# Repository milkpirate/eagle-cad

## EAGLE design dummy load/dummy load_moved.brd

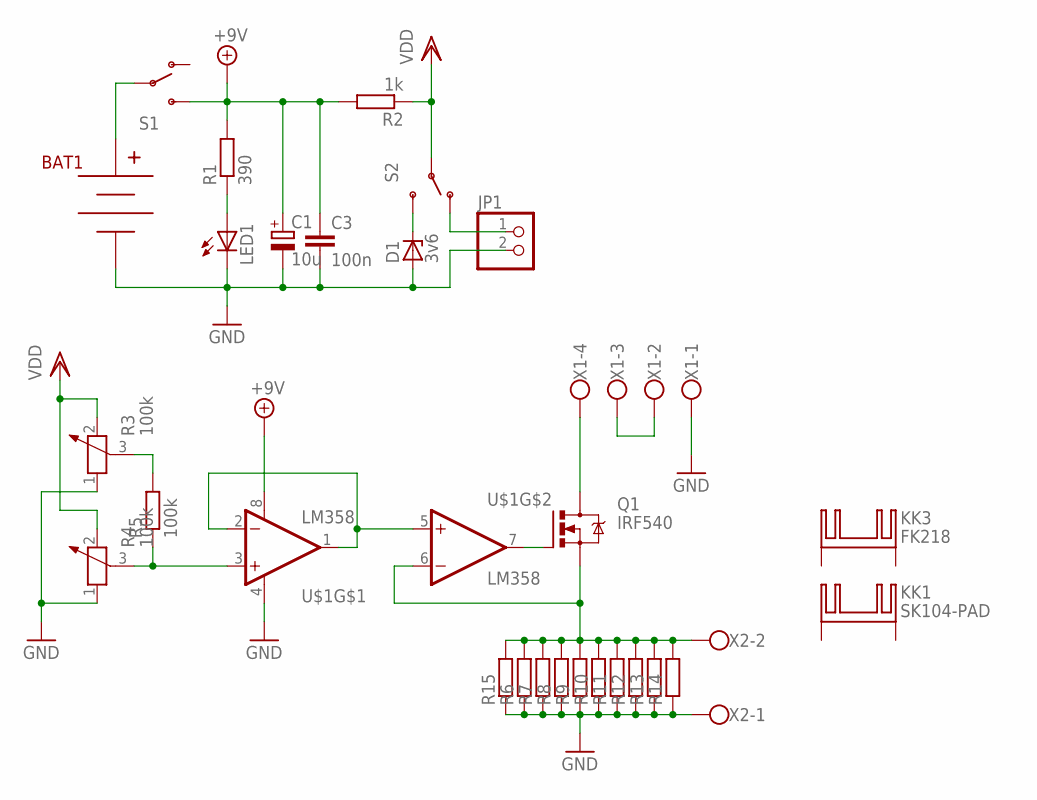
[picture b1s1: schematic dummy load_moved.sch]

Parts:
BAT1: BC9VPC
C1: 10u; TT2D5L
C3: 100n; C025-025X050
D1: 3v6; ZDIO-5
JP1: PINHD-1X2; 1X02
KK1: SK104-PAD
KK3: FK218
LED1: LED5MM
Q1: IRF540; TO220BV
R1: 390; 0204/7
R2: 1k; 0204/7
R3, R4: 100k; PT-10
R5: 100k; 0204/7
R6, R7, R8, R9, R10, R11, R12, R13, R14, R15: R-EU_0207/7; 0207/7
S1, S2: SWITCH-SPSTPTH; SWITCH-SPDT
U$1: LM358; DIP08
X1: W237-4
X2: W237-102

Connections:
+9V: C1.+, C3.1, R1.2, R2.2, S1.3 (S), U$1.8 (V+)
GND: BAT1.V-, C1.-, C3.2, D1.A, JP1.2, LED1.K (C), R3.1, R4.1, R6.1, R7.1, R8.1, R9.1, R10.1, R11.1, R12.1, R13.1, R14.1, R15.1, U$1.4 (V-), X1.1, X2.1
unnamed: U$1.1 (OUT), U$1.2 (-IN), U$1.5 (+IN)
unnamed: R4.3, R5.1, U$1.3 (+IN)
unnamed: LED1.A, R1.1
unnamed: R3.3, R5.2
unnamed: BAT1.V+, S1.2
unnamed: Q1.D, X1.4
unnamed: X1.2, X1.3
unnamed: Q1.G, U$1.7 (OUT)
unnamed: D1.C, S2.3 (S)
unnamed: JP1.1, S2.1 (O)
unnamed: Q1.S, R6.2, R7.2, R8.2, R9.2, R10.2, R11.2, R12.2, R13.2, R14.2, R15.2, U$1.6 (-IN), X2.2
VDD: R2.1, R3.2, R4.2, S2.2

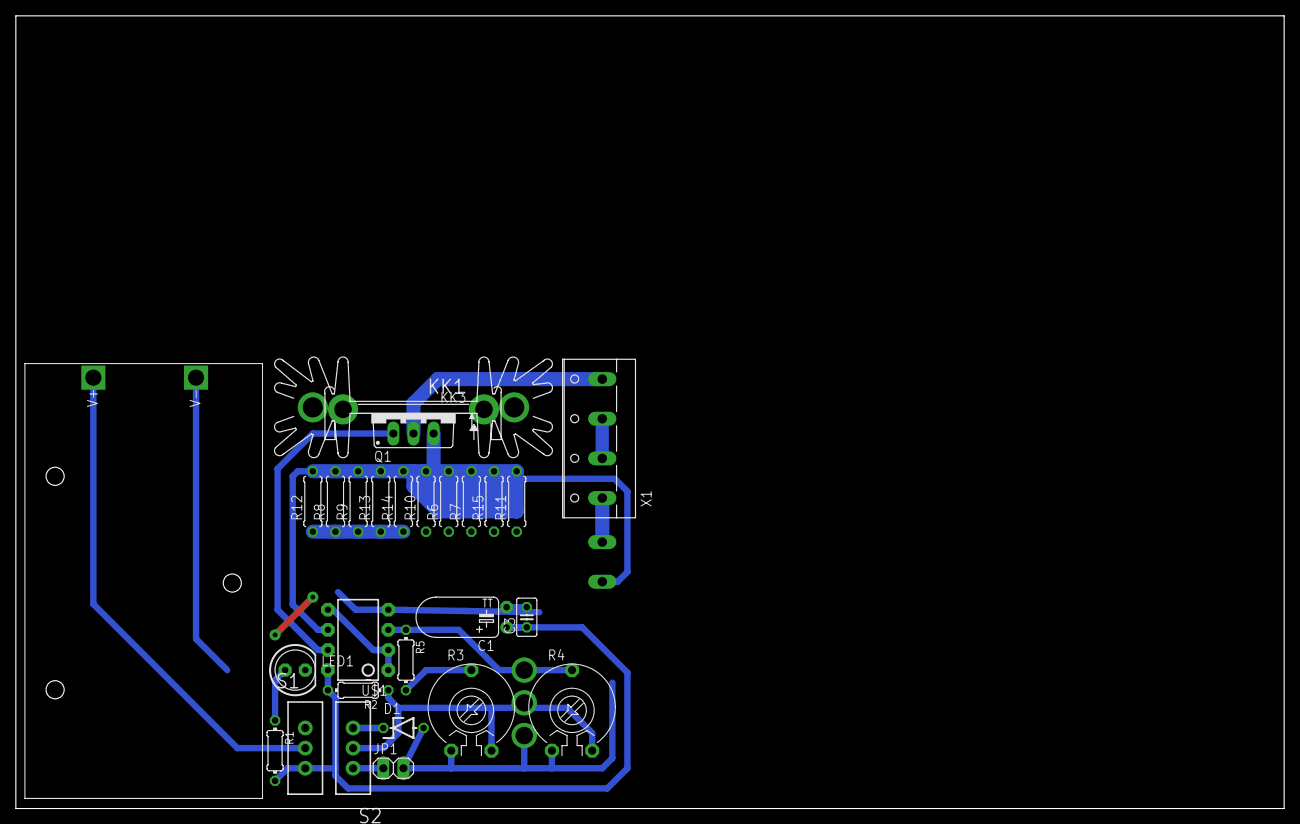
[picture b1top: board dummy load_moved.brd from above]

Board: 2 copper layers, 160.0 x 100.0 mm, 29 parts (1 on the bottom side), 14 nets.

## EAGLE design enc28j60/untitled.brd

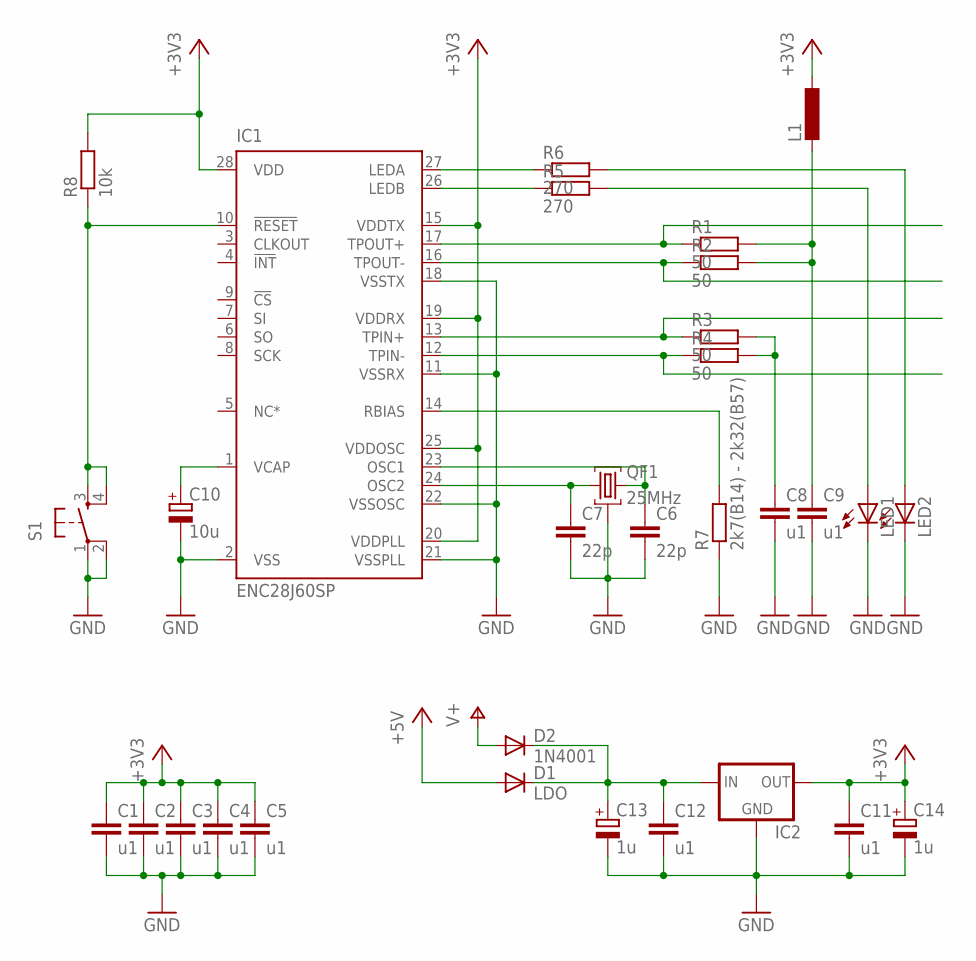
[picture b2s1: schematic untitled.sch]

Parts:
C1, C2, C3, C4, C5, C8, C9, C11, C12: u1; C025-025X050
C6, C7: 22p; C025-025X050
C10: 10u; E2,5-6
C13, C14: 1u; E2,5-6
D1: LDO; D-2.5
D2: 1N4001; D-2.5
IC1: ENC28J60SP; DIL28-3
IC2: MCP1700_TO92-INLINE; TO92-
L1: L-EU0204/5; 0204/5
LED1, LED2: LED5MM
QF1: 25MHz; HC49U
R1, R2, R3, R4: 50; 0204/7
R5, R6: 270; 0204/7
R7: 2k7(B14) - 2k32(B57); 0204/7
R8: 10k; 0204V
S1: TAC_SWITCHPTH; TACTILE-PTH

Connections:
+3V3: C1.1, C2.1, C3.1, C4.1, C5.1, C11.1, C14.+, IC1.15 (VDDTX), IC1.19 (VDDRX), IC1.20 (VDDPLL), IC1.25 (VDDOSC), IC1.28 (VDD), IC2.3 (OUT), L1.1, R8.2
+5V: D1.A
GND: C1.2, C2.2, C3.2, C4.2, C5.2, C6.2, C7.2, C8.2, C9.2, C10.-, C11.2, C12.2, C13.-, C14.-, IC1.2 (VSS), IC1.11 (VSSRX), IC1.18 (VSSTX), IC1.21 (VSSPLL), IC1.22 (VSSOSC), IC2.1 (GND), LED1.K (C), LED2.K (C), QF1.2, R7.1, S1.1, S1.2
unnamed: C10.+, IC1.1 (VCAP)
unnamed: C8.1, R3.2, R4.2
unnamed: IC1.27 (LEDA), R6.1
unnamed: IC1.26 (LEDB), R5.1
unnamed: IC1.17 (TPOUT+), R1.1
unnamed: C7.1, IC1.24 (OSC2), QF1.1
unnamed: C6.1, IC1.23 (OSC1), QF1.3
unnamed: IC1.16 (TPOUT-), R2.1
unnamed: IC1.14 (RBIAS), R7.2
unnamed: IC1.13 (TPIN+), R3.1
unnamed: IC1.12 (TPIN-), R4.1
unnamed: LED1.A, R5.2
unnamed: C9.1, L1.2, R1.2, R2.2
unnamed: LED2.A, R6.2
unnamed: C12.1, C13.+, D1.C, D2.C, IC2.2 (IN)
unnamed: IC1.10 (!RESET), R8.1, S1.3, S1.4
V+: D2.A

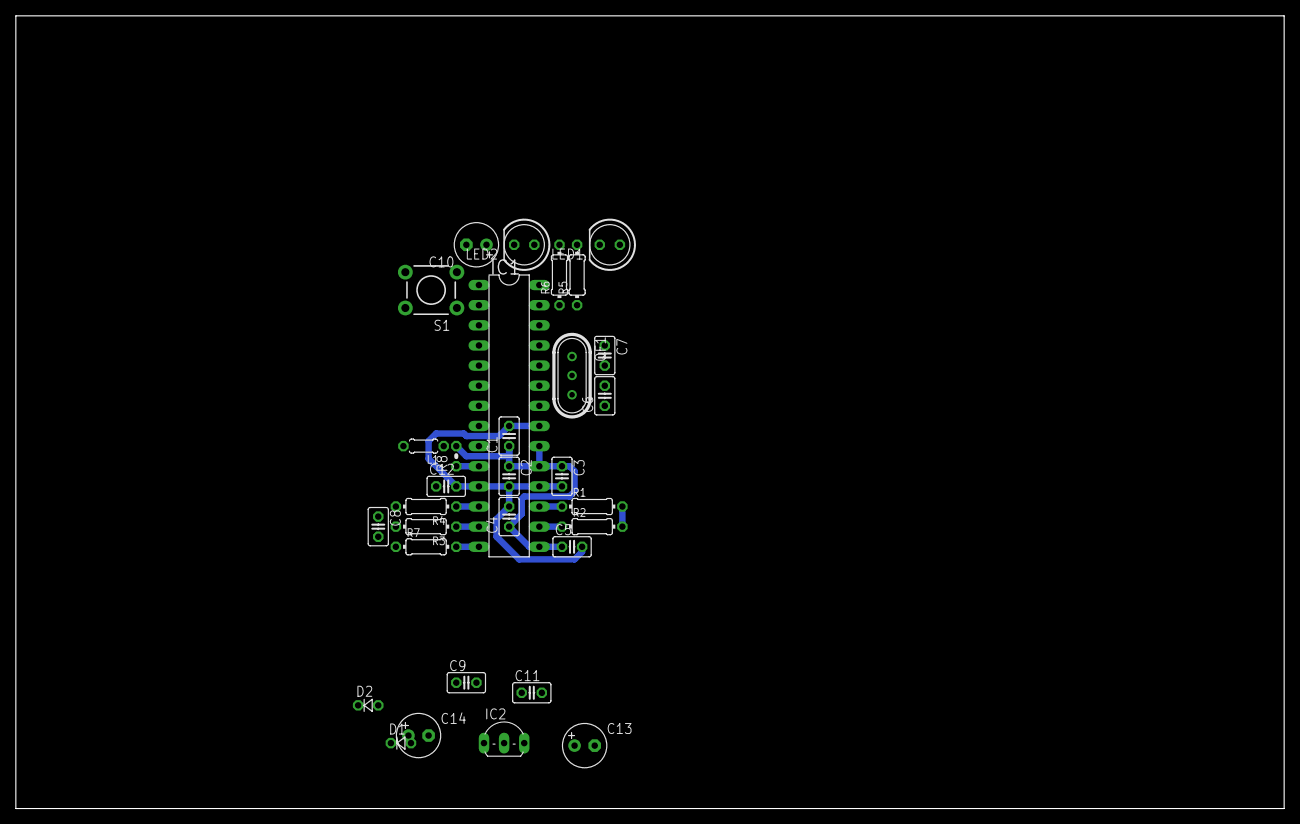
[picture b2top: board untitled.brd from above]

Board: 2 copper layers, 160.0 x 100.0 mm, 31 parts (0 on the bottom side), 18 nets.

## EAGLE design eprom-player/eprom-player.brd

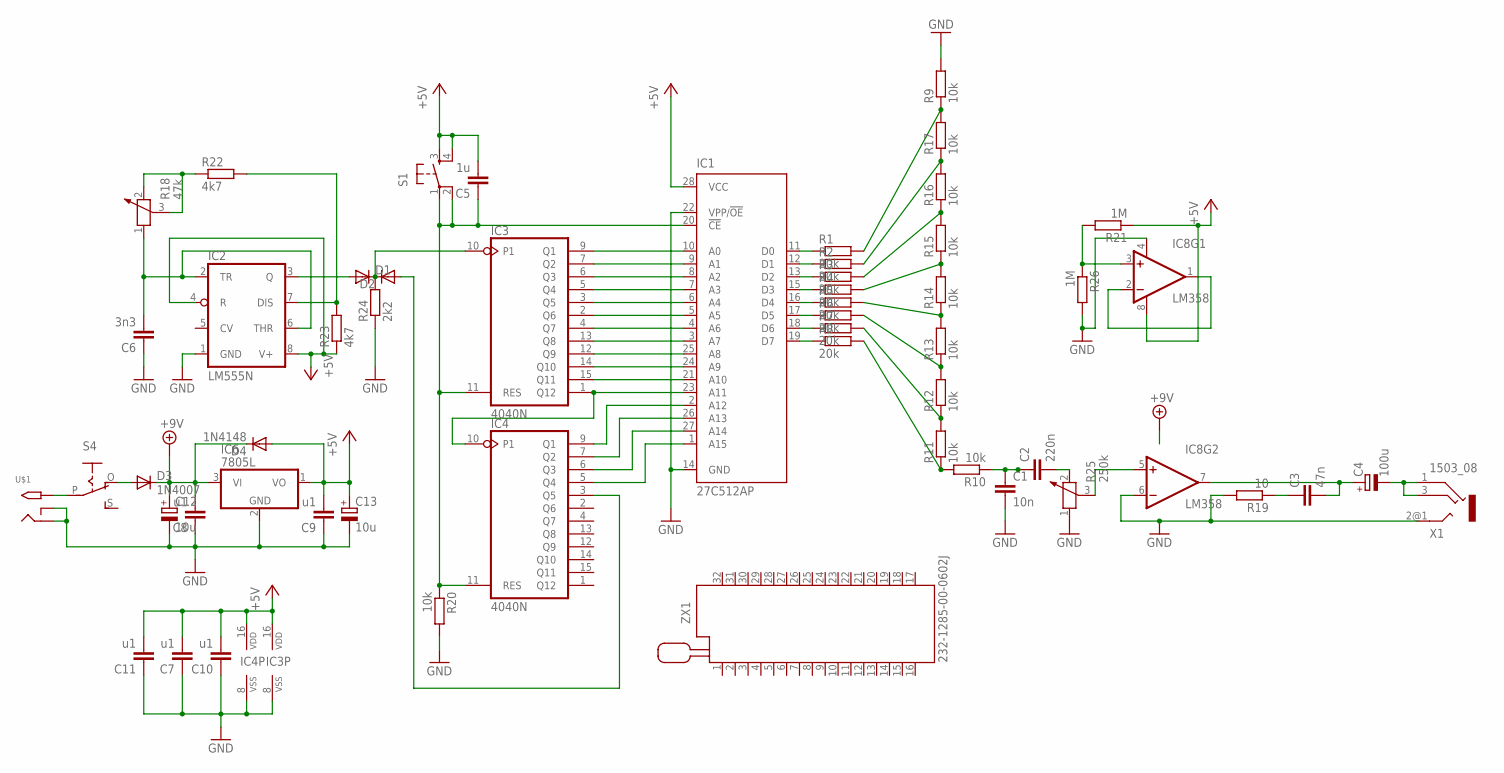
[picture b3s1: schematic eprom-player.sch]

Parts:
C1: 10n; C025-025X050
C2: 220n; C025-025X050
C3: 47n; C025-025X050
C4: 100u; E2,5-5
C5: 1u; C025-025X050
C6: 3n3; C025-025X050
C7, C8, C9, C10, C11: u1; C025-025X050
C12, C13: 10u; E2,5-6
D1, D2: DIODE-D-7.5; D-7.5
D3: 1N4007; D-2.5
D4: 1N4148; D-2.5
IC1: 27C512AP; DIL28-6
IC2: LM555N; DIL08-ROUND
IC3, IC4: 4040N; DIL16
IC6: 7805L; TO92
IC8: LM358; DIP08
R1, R2, R3: 20k; 0204/7
R4, R5, R6, R7, R8: 20k; 0204V
R9, R10, R11, R12, R13, R14, R15, R16, R17, R20: 10k; 0204V
R18: 47k; PT-10
R19: 10; 0204/5
R21, R26: 1M; 0204V
R22, R23: 4k7; 0204V
R24: 2k2; 0204V
R25: 250k; PT-10
S1: TAC_SWITCHPTH; TACTILE-PTH
S4: EG1218S; EG1218
U$1: 2.1MMJACKTHM; PJ-102A
X1: 1503_08
ZX1: 232-1285-00-0602J

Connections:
+5V: C5.2, C7.2, C9.2, C10.2, C11.2, C13.+, D4.A, IC1.28 (VCC), IC2.4 (R), IC2.8 (V+), IC3.16 (VDD), IC4.16 (VDD), IC6.1 (VO), IC8.8 (V+), R21.1, R23.1, S1.3, S1.4
+9V: C8.2, C12.+, D3.C, D4.C, IC6.3 (VI)
GND: C1.2, C6.1, C7.1, C8.1, C9.1, C10.1, C11.1, C12.-, C13.-, IC1.14 (GND), IC1.22 (VPP/!OE), IC2.1 (GND), IC3.8 (VSS), IC4.8 (VSS), IC6.2 (GND), IC8.4 (V-), IC8.6 (-IN), R9.2, R19.2, R20.2, R24.1, R25.1, R26.2, U$1.RING, U$1.RING_SW, X1.2@1 (2)
unnamed: IC1.11 (D0), R1.1
unnamed: IC1.12 (D1), R2.1
unnamed: IC1.13 (D2), R3.1
unnamed: IC1.15 (D3), R4.1
unnamed: IC1.16 (D4), R5.1
unnamed: IC1.17 (D5), R6.1
unnamed: IC1.18 (D6), R7.1
unnamed: IC1.19 (D7), R8.1
unnamed: IC1.23 (A11), IC3.1 (Q12), IC4.10 (P1)
unnamed: IC1.5 (A5), IC3.2 (Q6)
unnamed: IC1.6 (A4), IC3.3 (Q5)
unnamed: IC1.4 (A6), IC3.4 (Q7)
unnamed: IC1.7 (A3), IC3.5 (Q4)
unnamed: IC1.8 (A2), IC3.6 (Q3)
unnamed: IC1.9 (A1), IC3.7 (Q2)
unnamed: IC1.10 (A0), IC3.9 (Q1)
unnamed: IC1.25 (A8), IC3.12 (Q9)
unnamed: IC1.3 (A7), IC3.13 (Q8)
unnamed: IC1.24 (A9), IC3.14 (Q10)
unnamed: IC1.21 (A10), IC3.15 (Q11)
unnamed: IC1.2 (A12), IC4.9 (Q1)
unnamed: IC1.26 (A13), IC4.7 (Q2)
unnamed: IC1.27 (A14), IC4.6 (Q3)
unnamed: IC1.1 (A15), IC4.5 (Q4)
unnamed: R8.2, R10.2, R11.1
unnamed: R7.2, R11.2, R12.1
unnamed: R5.2, R13.2, R14.1
unnamed: R4.2, R14.2, R15.1
unnamed: R2.2, R16.2, R17.1
unnamed: R6.2, R12.2, R13.1
unnamed: R3.2, R15.2, R16.1
unnamed: R1.2, R9.1, R17.2
unnamed: C1.1, C2.1, R10.1
unnamed: C2.2, R25.2
unnamed: C4.-, X1.1, X1.3
unnamed: IC8.5 (+IN), R25.3
unnamed: C3.1, R19.1
unnamed: C3.2, C4.+, IC8.7 (OUT)
unnamed: C5.1, IC1.20 (!CE), IC3.11 (RES), IC4.11 (RES), R20.1, S1.1, S1.2
unnamed: D1.C, D2.C, IC3.10 (P1), R24.2
unnamed: D1.A, IC2.3 (Q)
unnamed: C6.2, IC2.2 (TR), IC2.6 (THR), R18.1
unnamed: S4.P, U$1.TIP
unnamed: R18.2, R18.3, R22.1
unnamed: IC2.7 (DIS), R22.2, R23.2
unnamed: D2.A, IC4.3 (Q5)
unnamed: D3.A, S4.O
unnamed: IC8.1 (OUT), IC8.2 (-IN)
unnamed: IC8.3 (+IN), R21.2, R26.1

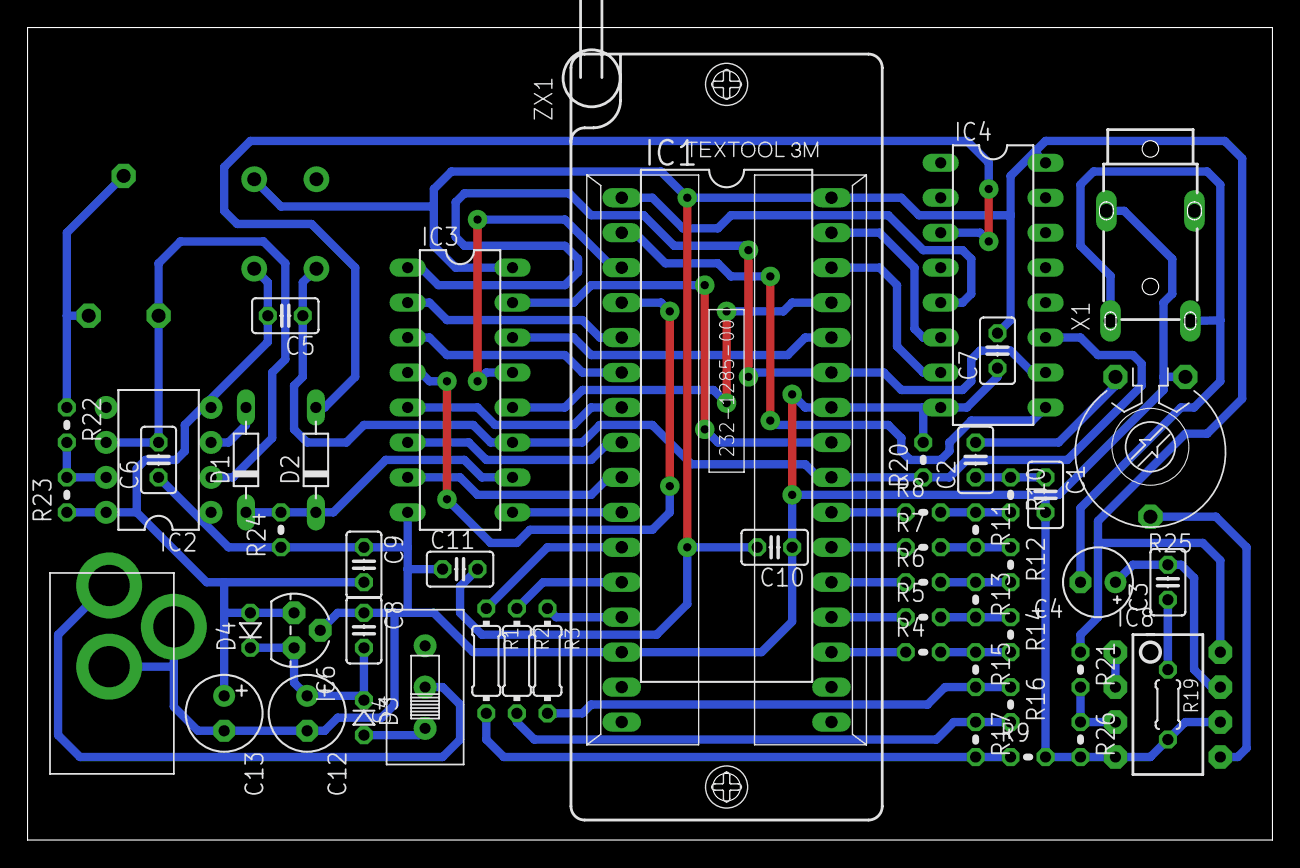
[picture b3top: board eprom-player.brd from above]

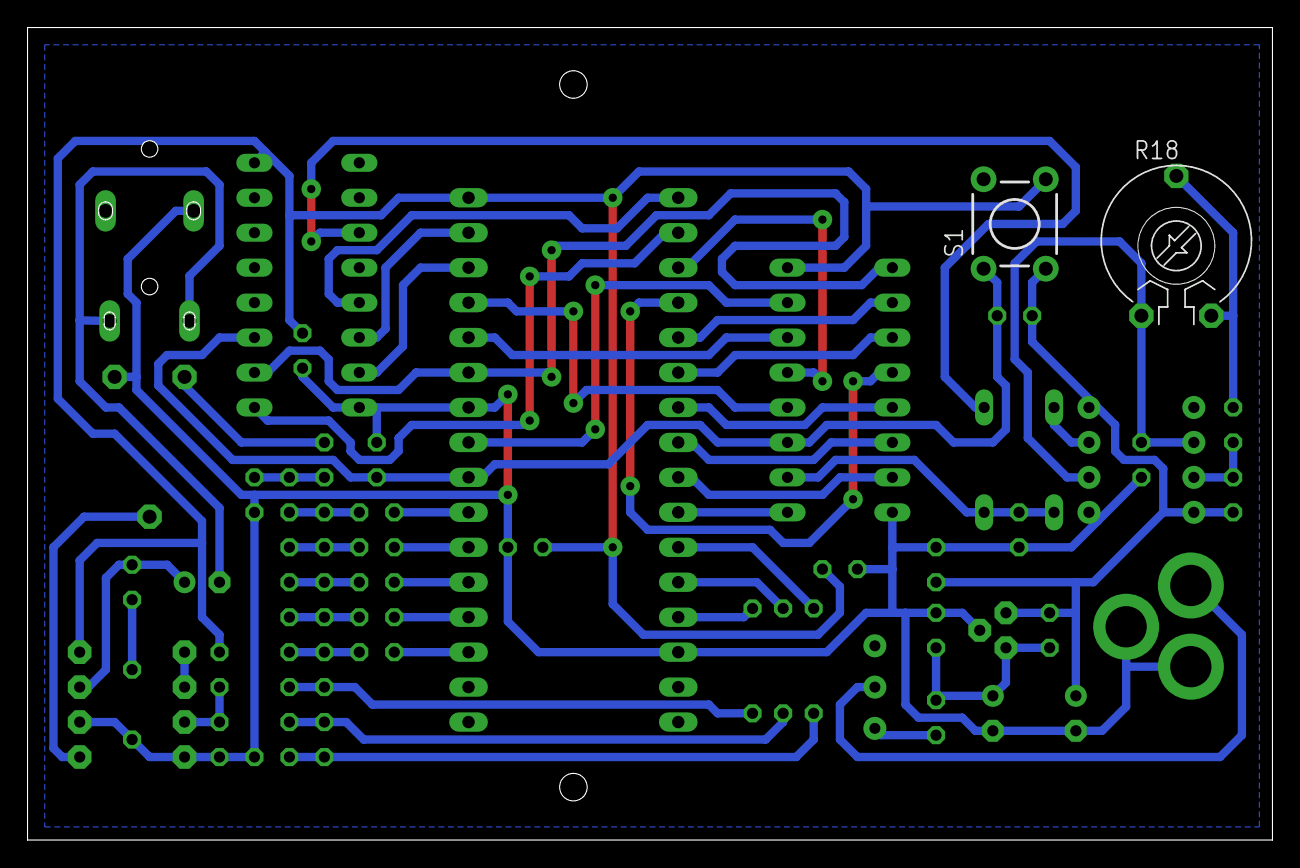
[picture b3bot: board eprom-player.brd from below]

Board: 2 copper layers, 90.5 x 59.0 mm, 54 parts (2 on the bottom side), 52 nets.

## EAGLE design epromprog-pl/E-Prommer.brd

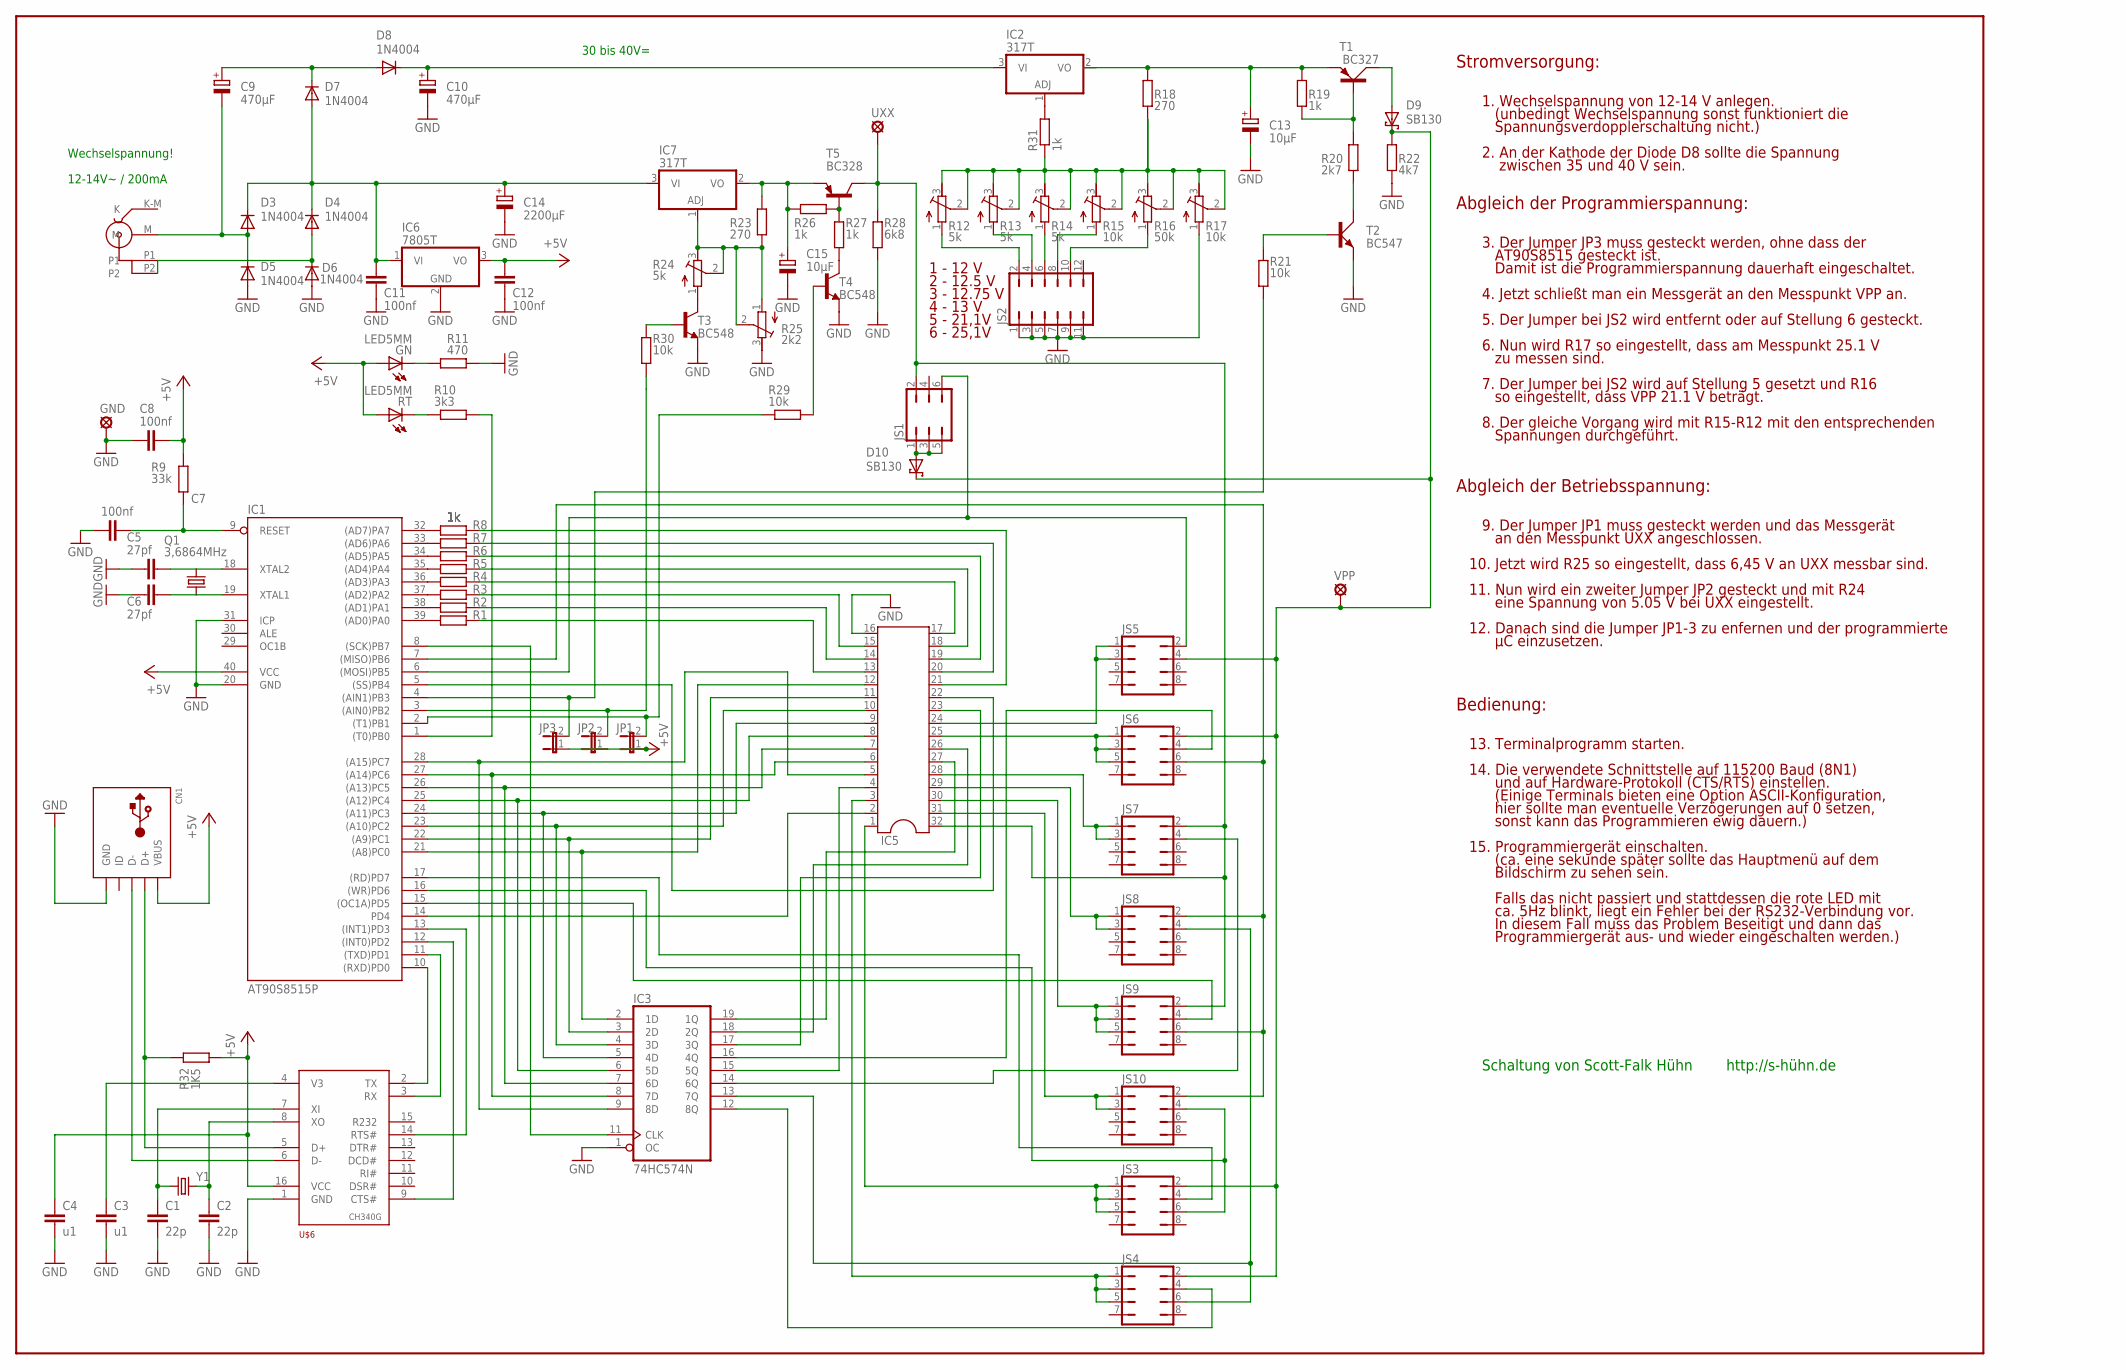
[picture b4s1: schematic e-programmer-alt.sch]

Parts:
BU1: KLIN_BU
C1, C2: 22p; C025-025X050
C3, C4: u1; C025-025X050
C5, C6: 27pf; C025-024X044
C7, C8, C11, C12: 100nf; C025-024X044
C9: 470µF; E3,5-10
C10: 470µF; E5-13
C13: 10µF; E2,5-5
C14: 2200µF; E7,5-16
C15: 10µF; E5-5
CN1: USBTHM; USB-MINIB-THM
D3, D4, D5, D6, D7, D8: 1N4004; DO41-10
D9, D10: SB130; DO35-7
GN: LED5MM
GND: LSP10
IC1: AT90S8515P; DIL40
IC2, IC7: 317T; TO220H
IC3: 74HC574N; DIL20
IC5: DIL32
IC6: 7805T; TO220H
JP1, JP2, JP3: JP1E; JP1
JS1: JP3Q
JS2: JP6Q
JS3, JS4, JS5, JS6, JS7, JS8, JS9, JS10: JP4Q
Q1: 3,6864MHz; HC49U-V
R1, R2, R3, R4, R5, R6, R7, R8, R19, R26, R27, R31: 1k; 0207/7
R9: 33k; 0204/7
R10: 3k3; 0204/7
R11: 470; 0204/7
R12, R13, R14, R24: 5k; RTRIM3296Y
R15, R17: 10k; RTRIM3296Y
R16: 50k; RTRIM3296Y
R18, R23: 270; 0207/7
R20: 2k7; 0207/7
R21, R29, R30: 10k; 0207/7
R22: 4k7; 0207/7
R25: 2k2; RTRIM3296Y
R28: 6k8; 0207/7
R32: 1K5; 0204/7
RT: LED5MM
T1: BC327; SOT54A
T2: BC547; SOT54A
T3, T4: BC548; TO92
T5: BC328; TO92
U$6: CH340G; SO16
UXX: LSP10
VPP: LSP10
Y1: CRYSTALHC49US; HC49US

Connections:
!CE: IC1.5 ((SS)PB4), IC5.22
!OE: IC1.6 ((MOSI)PB5), JS1.6, JS5.2
!PR: IC1.7 ((MISO)PB6), JS6.6, JS8.2, JS9.6, JS10.2
+5V: C4.1, C8.2, C12.1, CN1.VBUS, GN.A, IC1.40 (VCC), IC6.3 (VO), JP1.1, JP2.1, JP3.1, R9.2, R32.1, RT.A, U$6.16 (VCC); also elsewhere on the board
A0: IC1.21 ((A8)PC0), IC3.2 (1D), IC5.12
A1: IC1.22 ((A9)PC1), IC3.3 (2D), IC5.11
A2: IC1.23 ((A10)PC2), IC3.4 (3D), IC5.10
A3: IC1.24 ((A11)PC3), IC3.5 (4D), IC5.9
A4: IC1.25 ((A12)PC4), IC3.6 (5D), IC5.8
A5: IC1.26 ((A13)PC5), IC3.7 (6D), IC5.7
A6: IC1.27 ((A14)PC6), IC3.8 (7D), IC5.6
A7: IC1.28 ((A15)PC7), IC3.9 (8D), IC5.5
A8: IC3.19 (1Q), IC5.27
A9: IC3.18 (2Q), IC5.26
A10: IC3.17 (3Q), IC5.23
A11: IC3.16 (4Q), JS6.4
A12: IC3.15 (5Q), IC5.4
A13: IC3.14 (6Q), JS7.4
A14: IC3.13 (7Q), JS4.6, JS8.4
A15: IC3.12 (8Q), JS4.4
A16: IC1.14 (PD4), IC5.2
A17: IC1.15 ((OC1A)PD5), JS9.4
A18: IC1.16 ((WR)PD6), JS3.6, JS10.4
A19: IC1.17 ((RD)PD7), JS3.4
CTS: IC1.12 ((INT0)PD2), U$6.9 (CTS#); also elsewhere on the board
D0: IC5.13, R1.2
D1: IC5.14, R2.2
D2: IC5.15, R3.2
D3: IC5.17, R4.2
D4: IC5.18, R5.2
D5: IC5.19, R6.2
D6: IC5.20, R7.2
D7: IC5.21, R8.2
GND: C1.2, C2.2, C3.2, C4.2, C5.1, C6.1, C7.1, C8.1, C10.-, C11.2, C12.2, C13.-, C14.-, C15.-, CN1.GND, D5.A, D6.A, GND.MP, IC1.20 (GND), IC1.31 (ICP), IC3.1 (OC), IC5.16, IC6.2 (GND), JS2.1, JS2.3, JS2.5, JS2.7, JS2.9, JS2.11, R11.2, R17.1 (E), R22.1, R25.3 (A), R28.1, T2.E, T3.1 (E), T4.1 (E), U$6.1 (GND); also elsewhere on the board
unnamed: IC1.32 ((AD7)PA7), R8.1
unnamed: IC1.33 ((AD6)PA6), R7.1
unnamed: IC1.34 ((AD5)PA5), R6.1
unnamed: IC1.35 ((AD4)PA4), R5.1
unnamed: IC1.36 ((AD3)PA3), R4.1
unnamed: IC1.37 ((AD2)PA2), R3.1
unnamed: IC1.38 ((AD1)PA1), R2.1
unnamed: IC1.39 ((AD0)PA0), R1.1
unnamed: IC1.8 ((SCK)PB7), IC3.11 (CLK)
unnamed 43: IC1.10 ((RXD)PD0), U$6.2 (TX); also elsewhere on the board
unnamed 44: IC1.11 ((TXD)PD1), U$6.3 (RX); also elsewhere on the board
unnamed: CN1.D+, R32.2, U$6.5 (D+)
unnamed: CN1.D-, U$6.6 (D-)
unnamed: C2.1, U$6.8 (XO), Y1.2
unnamed: C1.1, U$6.7 (XI), Y1.1
unnamed: C3.1, U$6.4 (V3)
unnamed: R10.1, RT.K (C)
unnamed: GN.K (C), R11.1
unnamed: IC5.3, JS4.1, JS4.3, JS4.5
unnamed: IC5.1, JS3.1, JS3.3, JS3.5
unnamed: IC5.24, JS5.1, JS5.3
unnamed: C7.2, IC1.9 (RESET), R9.1
unnamed: IC5.25, JS6.1, JS6.3, JS6.5
unnamed: JS2.2, R12.1 (E)
unnamed: JS2.4, R13.1 (E)
unnamed: IC5.28, JS7.1, JS7.3
unnamed: IC5.29, JS8.1, JS8.3
unnamed: IC1.1 ((T0)PB0), R10.2
unnamed: IC5.30, JS9.1, JS9.3, JS9.5
unnamed: JS2.6, R14.1 (E)
unnamed: IC5.31, JS10.1, JS10.3
unnamed: JS2.8, R15.1 (E)
unnamed: JS2.10, R16.1 (E)
unnamed 71: R12.2 (S), R12.3 (A), R13.2 (S), R13.3 (A), R14.2 (S), R14.3 (A), R15.2 (S), R15.3 (A), R16.2 (S), R16.3 (A), R17.2 (S), R17.3 (A), R18.1, R31.1; also elsewhere on the board
unnamed: D10.A, JS1.1, JS1.3, JS1.5
unnamed: D9.A, T1.C
unnamed: R26.1, R27.2, T5.2 (B)
unnamed: R27.1, T4.3 (C)
unnamed: IC7.1 (ADJ), R23.1, R24.2 (S), R24.3 (A), R25.1 (E), R25.2 (S)
unnamed: R24.1 (E), T3.3 (C)
unnamed: C15.+, IC7.2 (VO), R23.2, R26.2, T5.1 (E)
unnamed: R29.2, T4.2 (B)
unnamed: C13.+, IC2.2 (VO), R18.2, R19.2, T1.E
unnamed: R30.2, T3.2 (B)
unnamed: R19.1, R20.2, T1.B
unnamed: R20.1, T2.C
unnamed: R21.2, T2.B
unnamed: IC2.1 (ADJ), R31.2
RTS: IC1.13 ((INT1)PD3), U$6.14 (RTS#); also elsewhere on the board
UXX: IC5.32, JS1.2, JS7.2, JS9.2, R28.2, T5.3 (C), UXX.MP
VCC_5/6: IC1.3 ((AIN0)PB2), JP2.2, R30.1
VCC_EIN: IC1.2 ((T1)PB1), JP1.2, R29.1
VPP: D9.C, D10.C, JS3.2, JS4.2, JS5.4, JS6.2, R22.2, VPP.MP
VPP_EIN: IC1.4 ((AIN1)PB3), JP3.2, R21.1

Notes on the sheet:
12-14V~ / 200mA
Wechselspannung!
30 bis 40V=
Schaltung von Scott-Falk Hühn
http://s-hühn.de
1. Wechselspannung von 12-14 V anlegen.
(unbedingt Wechselspannung sonst funktioniert die
Spannungsverdopplerschaltung nicht.)
2. An der Kathode der Diode D8 sollte die Spannung
zwischen 35 und 40 V sein.
3. Der Jumper JP3 muss gesteckt werden, ohne dass der
4. Jetzt schließt man ein Messgerät an den Messpunkt VPP an.
5. Der Jumper bei JS2 wird entfernt oder auf Stellung 6 gesteckt.
6. Nun wird R17 so eingestellt, dass am Messpunkt 25.1 V
zu messen sind.
7. Der Jumper bei JS2 wird auf Stellung 5 gesetzt und R16
so eingestellt, dass VPP 21.1 V beträgt.
8. Der gleiche Vorgang wird mit R15-R12 mit den entsprechenden
Spannungen durchgeführt.
9. Der Jumper JP1 muss gesteckt werden und das Messgerät
an den Messpunkt UXX angeschlossen.
10. Jetzt wird R25 so eingestellt, dass 6,45 V an UXX messbar sind.
11. Nun wird ein zweiter Jumper JP2 gesteckt und mit R24
eine Spannung von 5.05 V bei UXX eingestellt.
Abgleich der Programmierspannung:
Abgleich der Betriebsspannung:
Bedienung:
13. Terminalprogramm starten.
14. Die verwendete Schnittstelle auf 115200 Baud (8N1)
und auf Hardware-Protokoll (CTS/RTS) einstellen.
(Einige Terminals bieten eine Option ASCII-Konfiguration,
hier sollte man eventuelle Verzögerungen auf 0 setzen,
sonst kann das Programmieren ewig dauern.)
15. Programmiergerät einschalten.
(ca. eine sekunde später sollte das Hauptmenü auf dem
Bildschirm zu sehen sein.
Falls das nicht passiert und stattdessen die rote LED mit
ca. 5Hz blinkt, liegt ein Fehler bei der RS232-Verbindung vor.
In diesem Fall muss das Problem Beseitigt und dann das
Programmiergerät aus- und wieder eingeschalten werden.)

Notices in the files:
parts and their libraries:
SparkFun: Licensing: CC v3.0 Share-Alike You are welcome to use this library for commercial purposes.
SparkFun-AnalogIC: Licensing:Creative Commons ShareAlike 4.0 International - https://creativecommons.org/licenses/by-sa/4.0
